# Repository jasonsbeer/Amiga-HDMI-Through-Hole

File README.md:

# Amiga Video Slot to HDMI with Through Hole Components
This project was inspired by the [Amiga Digital Video](https://github.com/c0pperdragon/Amiga-Digital-Video) project by c0pperdragon. This design makes use of the Amiga 2000/3000 video slot and easy to solder through hole components, making it friendly for even the novice DIYer. At the time of writing this, all the components are available through DigiKey. This has been tested with both standard and Super Denise on Amiga 2000 rev 4.x and 6.x boards. The picture output is outstanding. It should be fully compatable with the Amiga 3000, but I do not have access to one for testing.

There are mounting holes to facilitate the use of a support bracket, which can be 3D printed. The bracket files can be found [here](/STL).

## PCB Ordering
The gerber files are available in the [Gerber](/Gerber) folder. Download the file and send to your preferred PCB manufacturer. I've been ordering mine through JLCPCB and have been happy with the results. Most of the options will be set directly from the Gerber file. For the rest, you can select these [options](JLCPCB-1.png).

## PCB Assembly
Order parts from the BOM list. I have included DigiKey part numbers for reference. Solder the components to the board, noting orientation of the sockets. You can solder the chips directly to the board, but I do not recommend this for DIY projects.

### v1.1 BOM
|Component|Package|Location|QTY|Source|Part Number|
--- | --- | --- | --- | --- | ---
SN74AHC86|14-DIP|U1|1|DigiKey|296-4627-5-ND
SN74AHC574|20-DIP|U2-3|2|DigiKey|296-4616-5-ND
LD1117AV33|TO-220-3|U4|1|DigiKey|497-1485-5-ND
14-DIP Socket|14-DIP|U1|1|DigiKey|AE9989-ND
20-DIP Socket|20-DIP|U2-3|2|DigiKey|AE9998-ND
0.1uF Ceramic Capacitor|Radial|C1-3,5|4|DigiKey|399-14065-1-ND
10uF Ceramic Capacitor|Radial|C4|1|DigiKey|445-181284-1-ND
40 Position Female Header|-|J1|1|DigiKey|S6104-ND
3x1 Male Header|-|JP1|1|DigiKey|732-5316-ND
Jumper|-|JP1|1|DigiKey|609-6251-ND
2x1 Male Header|-|J2|1|DigiKey|732-5315-ND
3.3k Resistor|Axial|R1|1|DigiKey|3.3KQBK-ND
Panel Mount HDMI Cable (optional)|-|-|1|DigiKey|1528-1575-ND
HDMI Mini to HDMI Adapter (optional)|-|-|1|DigiKey|1528-2481-ND

## Using The Card
You will need to supply a Raspberry Pi Zero and copy the correct program to a micro-SD card for the Pi to run. The standard (non-W) version of the Pi Zero works fine and is cheaper. You can obtain the current software release from the [RGBtoHDMI](https://github.com/hoglet67/RGBtoHDMI/releases) project page. Click on the link of the newest release, scroll to the bottom of the page, and download the zip file. Unzip and copy the files to the micro SD card and insert the micro SD card in the Pi Zero. Attach the Pi Zero to the video card, making sure to double check the orientation. The Pi Zero should be installed "face down", with pin 1 towards the "top" of the card. Installing the Pi incorrectly will likely kill it.

Set JP1 to match the Denise version in your Amiga. S.Denise = Super Denise (CSG 8373) or Denise (MOS 8362). An incorrect jumper setting will result in a low quality image. Connect an HDMI cable to the Raspberri Pi and to an HDMI or DVI monitor. If you do not have a support bracket, I strongly encourage you to place a peice of thin cardboard between the video card and the power supply of the Amiga 2000. Tape it in place to ensure the card will not short out on the power supply housing.

A momentary push button switch may be attached at J2 that will allow access to settings of the Pi software.

## Revision History
v1.0 Initial production release

v1.1 Routed /C1 and /C3 to U1. Delete U5 and R2

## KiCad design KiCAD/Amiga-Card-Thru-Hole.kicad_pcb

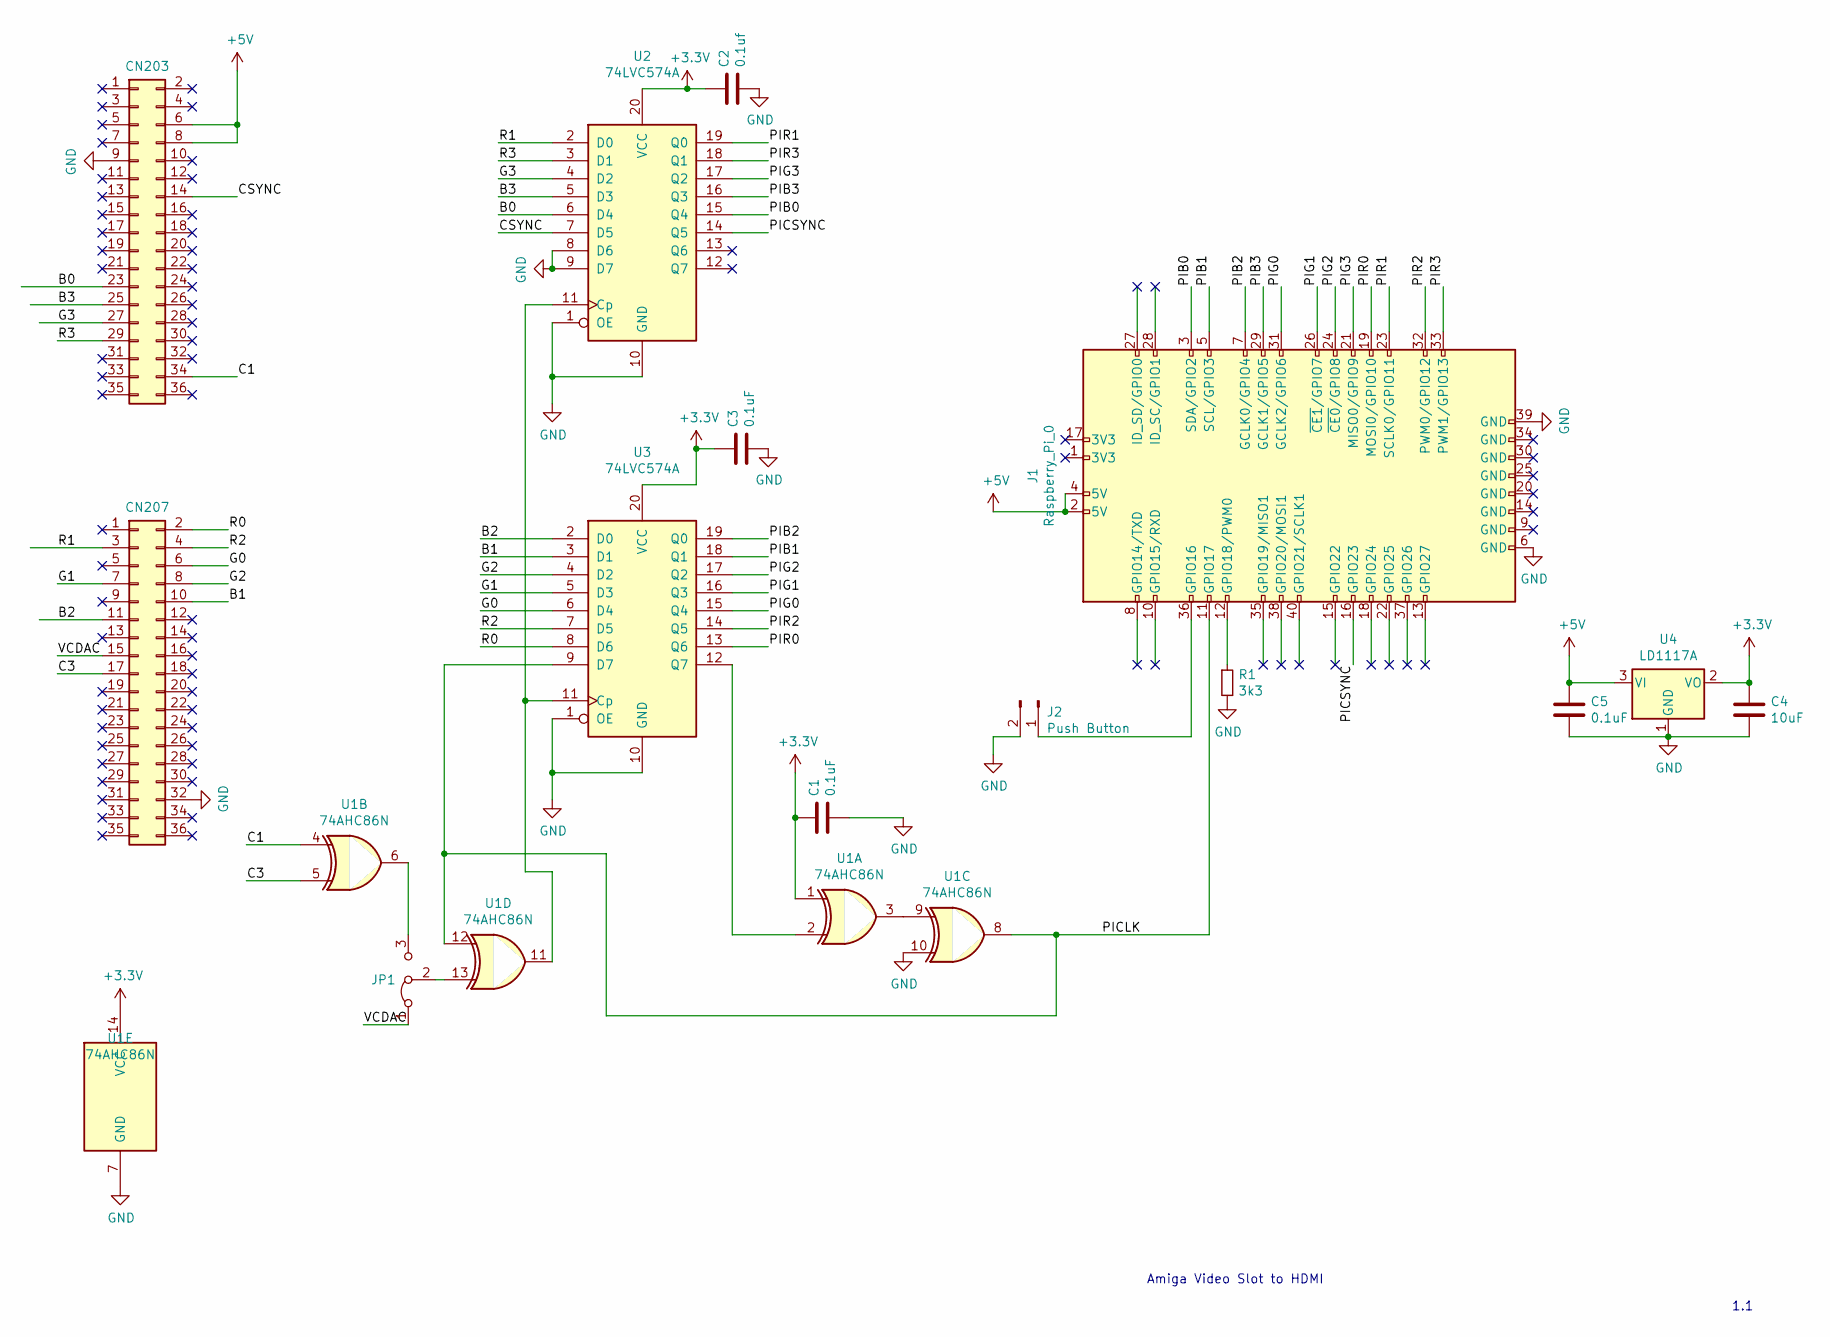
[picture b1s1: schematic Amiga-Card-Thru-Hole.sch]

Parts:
C1, C3, C5: 0.1uF; C_Disc_D7.5mm_W4.4mm_P5.00mm
C2: 0.1uf; C_Disc_D7.5mm_W4.4mm_P5.00mm
C4: 10uF; C_Disc_D7.5mm_W4.4mm_P5.00mm
CN203: CN203; Amiga 2x18 Card Edge Male
CN207: CN207; Amiga 2x18 Card Edge Male
J1: Raspberry_Pi_0; PinSocket_2x20_P2.54mm_Vertical
J2: Push Button; PinHeader_1x02_P2.54mm_Vertical
JP1: JP1; PinHeader_1x03_P2.54mm_Vertical
R1: 3k3; R_Axial_DIN0204_L3.6mm_D1.6mm_P7.62mm_Horizontal
U1: 74AHC86N; DIP-14_W7.62mm_Socket
U2, U3: 74LVC574A; DIP-20_W7.62mm_Socket
U4: LD1117A; TO-220-3_Horizontal_TabDown

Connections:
+3V3: C1.1, C2.1, C3.1, C4.1, U1.1, U1.14 (VCC), U2.20 (VCC), U3.20 (VCC), U4.2 (VO)
+5V: C5.1, CN203.6, CN203.8, J1.2 (5V), J1.4 (5V), U4.3 (VI)
/B0: CN203.23, U2.6 (D4)
/B1: CN207.10, U3.3 (D1)
/B2: CN207.11, U3.2 (D0)
/B3: CN203.25, U2.5 (D3)
/C1: CN203.34, U1.4
/C3: CN207.17, U1.5
/CSYNC: CN203.14, U2.7 (D5)
/G0: CN207.6, U3.6 (D4)
/G1: CN207.7, U3.5 (D3)
/G2: CN207.8, U3.4 (D2)
/G3: CN203.27, U2.4 (D2)
/PIB0: J1.3 (SDA/GPIO2), U2.15 (Q4)
/PIB1: J1.5 (SCL/GPIO3), U3.18 (Q1)
/PIB2: J1.7 (GCLK0/GPIO4), U3.19 (Q0)
/PIB3: J1.29 (GCLK1/GPIO5), U2.16 (Q3)
/PICLK: J1.11 (GPIO17), U1.8, U1.12, U3.9 (D7)
/PICSYNC: J1.16 (GPIO23), U2.14 (Q5)
/PIG0: J1.31 (GCLK2/GPIO6), U3.15 (Q4)
/PIG1: J1.26 (~CE1~/GPIO7), U3.16 (Q3)
/PIG2: J1.24 (~CE0~/GPIO8), U3.17 (Q2)
/PIG3: J1.21 (MISO0/GPIO9), U2.17 (Q2)
/PIR0: J1.19 (MOSI0/GPIO10), U3.13 (Q6)
/PIR1: J1.23 (SCLK0/GPIO11), U2.19 (Q0)
/PIR2: J1.32 (PWM0/GPIO12), U3.14 (Q5)
/PIR3: J1.33 (PWM1/GPIO13), U2.18 (Q1)
/R0: CN207.2, U3.8 (D6)
/R1: CN207.3, U2.2 (D0)
/R2: CN207.4, U3.7 (D5)
/R3: CN203.29, U2.3 (D1)
/VCDAC: CN207.15, JP1.1 (A)
GND: C1.2, C2.2, C3.2, C4.2, C5.2, CN203.9, CN207.32, J1.6 (GND), J1.39 (GND), J2.2, R1.2, U1.7 (GND), U1.10, U2.1 (OE), U2.8 (D6), U2.9 (D7), U2.10 (GND), U3.1 (OE), U3.10 (GND), U4.1 (GND)
unnamed: J1.12 (GPIO18/PWM0), R1.1
unnamed: J1.36 (GPIO16), J2.1
unnamed: JP1.2 (C), U1.13
unnamed: JP1.3 (B), U1.6
unnamed: U1.2, U3.12 (Q7)
unnamed: U1.3, U1.9
unnamed: U1.11, U2.11 (Cp), U3.11 (Cp)

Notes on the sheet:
1.1
Amiga Video Slot to HDMI

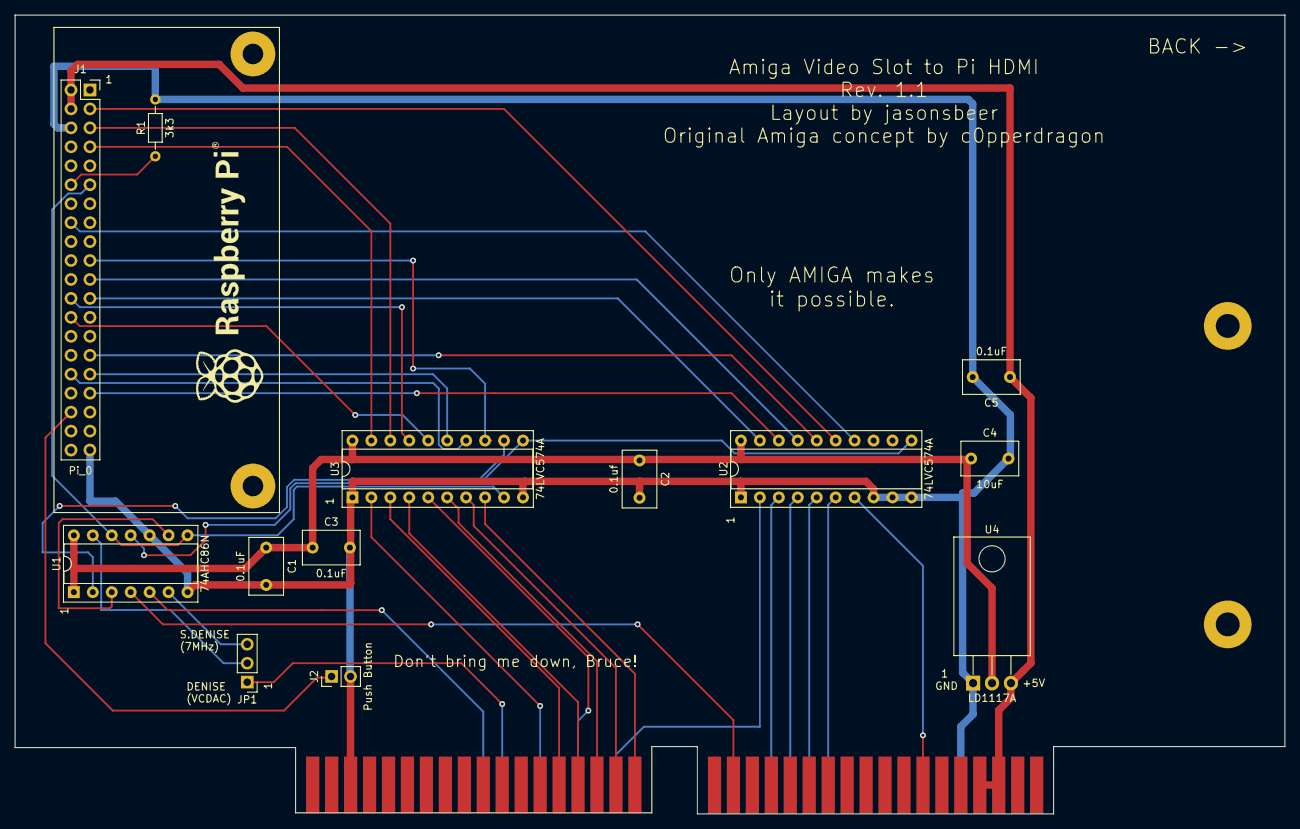
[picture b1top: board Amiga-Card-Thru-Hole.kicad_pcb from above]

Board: 2 copper layers, 170.2 x 107.1 mm, 15 parts (0 on the bottom side), 40 nets.

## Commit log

2021-03-03 Create x
2021-08-02 Add Amiga 2000 EATX Bracket Files
